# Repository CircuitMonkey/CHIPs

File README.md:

# CHIPs (aka CHIPz)

CHIPz modules are sub-circuits cooked down into a SMT module with a Cyberpunk Tech aesthetic.

The edge contacts are castelated and resemble the edge of a postage stamp.  Like similar modules on the market, CHIPs are designed to be soldered to a larger PCB board.  One advantage of the CHIPz modules is that a design can be revised or re-engineered to improve a larger design without having to redesign the whole system.  CHIPz also makes it convenient to pre-build smaller modules with common or repetive functions and use them over and over in other larger designs.

Almost all of the numbered designs were designed in EagleCAD and were intended to be sold into the hobby electronics market.  Alas, I have given up on that dream, but offer these designs for anyone who wishes to use them or just study the things I have made over the years. My current and future designs are now made with KiCAD.

I still design CHIPz modules and other things, but not for the purpose of manufacturing or selling.  I use the modules in my own creations and wish to share those things for anyone who has a similar need or wishes to simply understand the workings of these things.

If you wish to simply make a module, you can generally upload the Eagle BRD or KiCAD_PCB file directly to [OSH Park PCB](https://OSHPark.com) for preview and fabrication.

Everyting here is open source with minimal (if at all) license requirements.  Copy, mash-up and use to your hearts content.

## NOTE
New designs will be placed in a sub-directory, like [Synth] is.  Older designs will be moved eventually into a sub-folder but for now will dominate the file listing you see.

Enjoy,

Mark Koch  (Circuit Monkey)

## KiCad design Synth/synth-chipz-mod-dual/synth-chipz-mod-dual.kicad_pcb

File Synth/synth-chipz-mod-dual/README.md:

# Synth Module -- VCO/VCF Modulator

This module is a CHIPz implementation of a Modulator core for VCO and VCF functions.  It is originally based on a Modulator circuit from a Moog device.

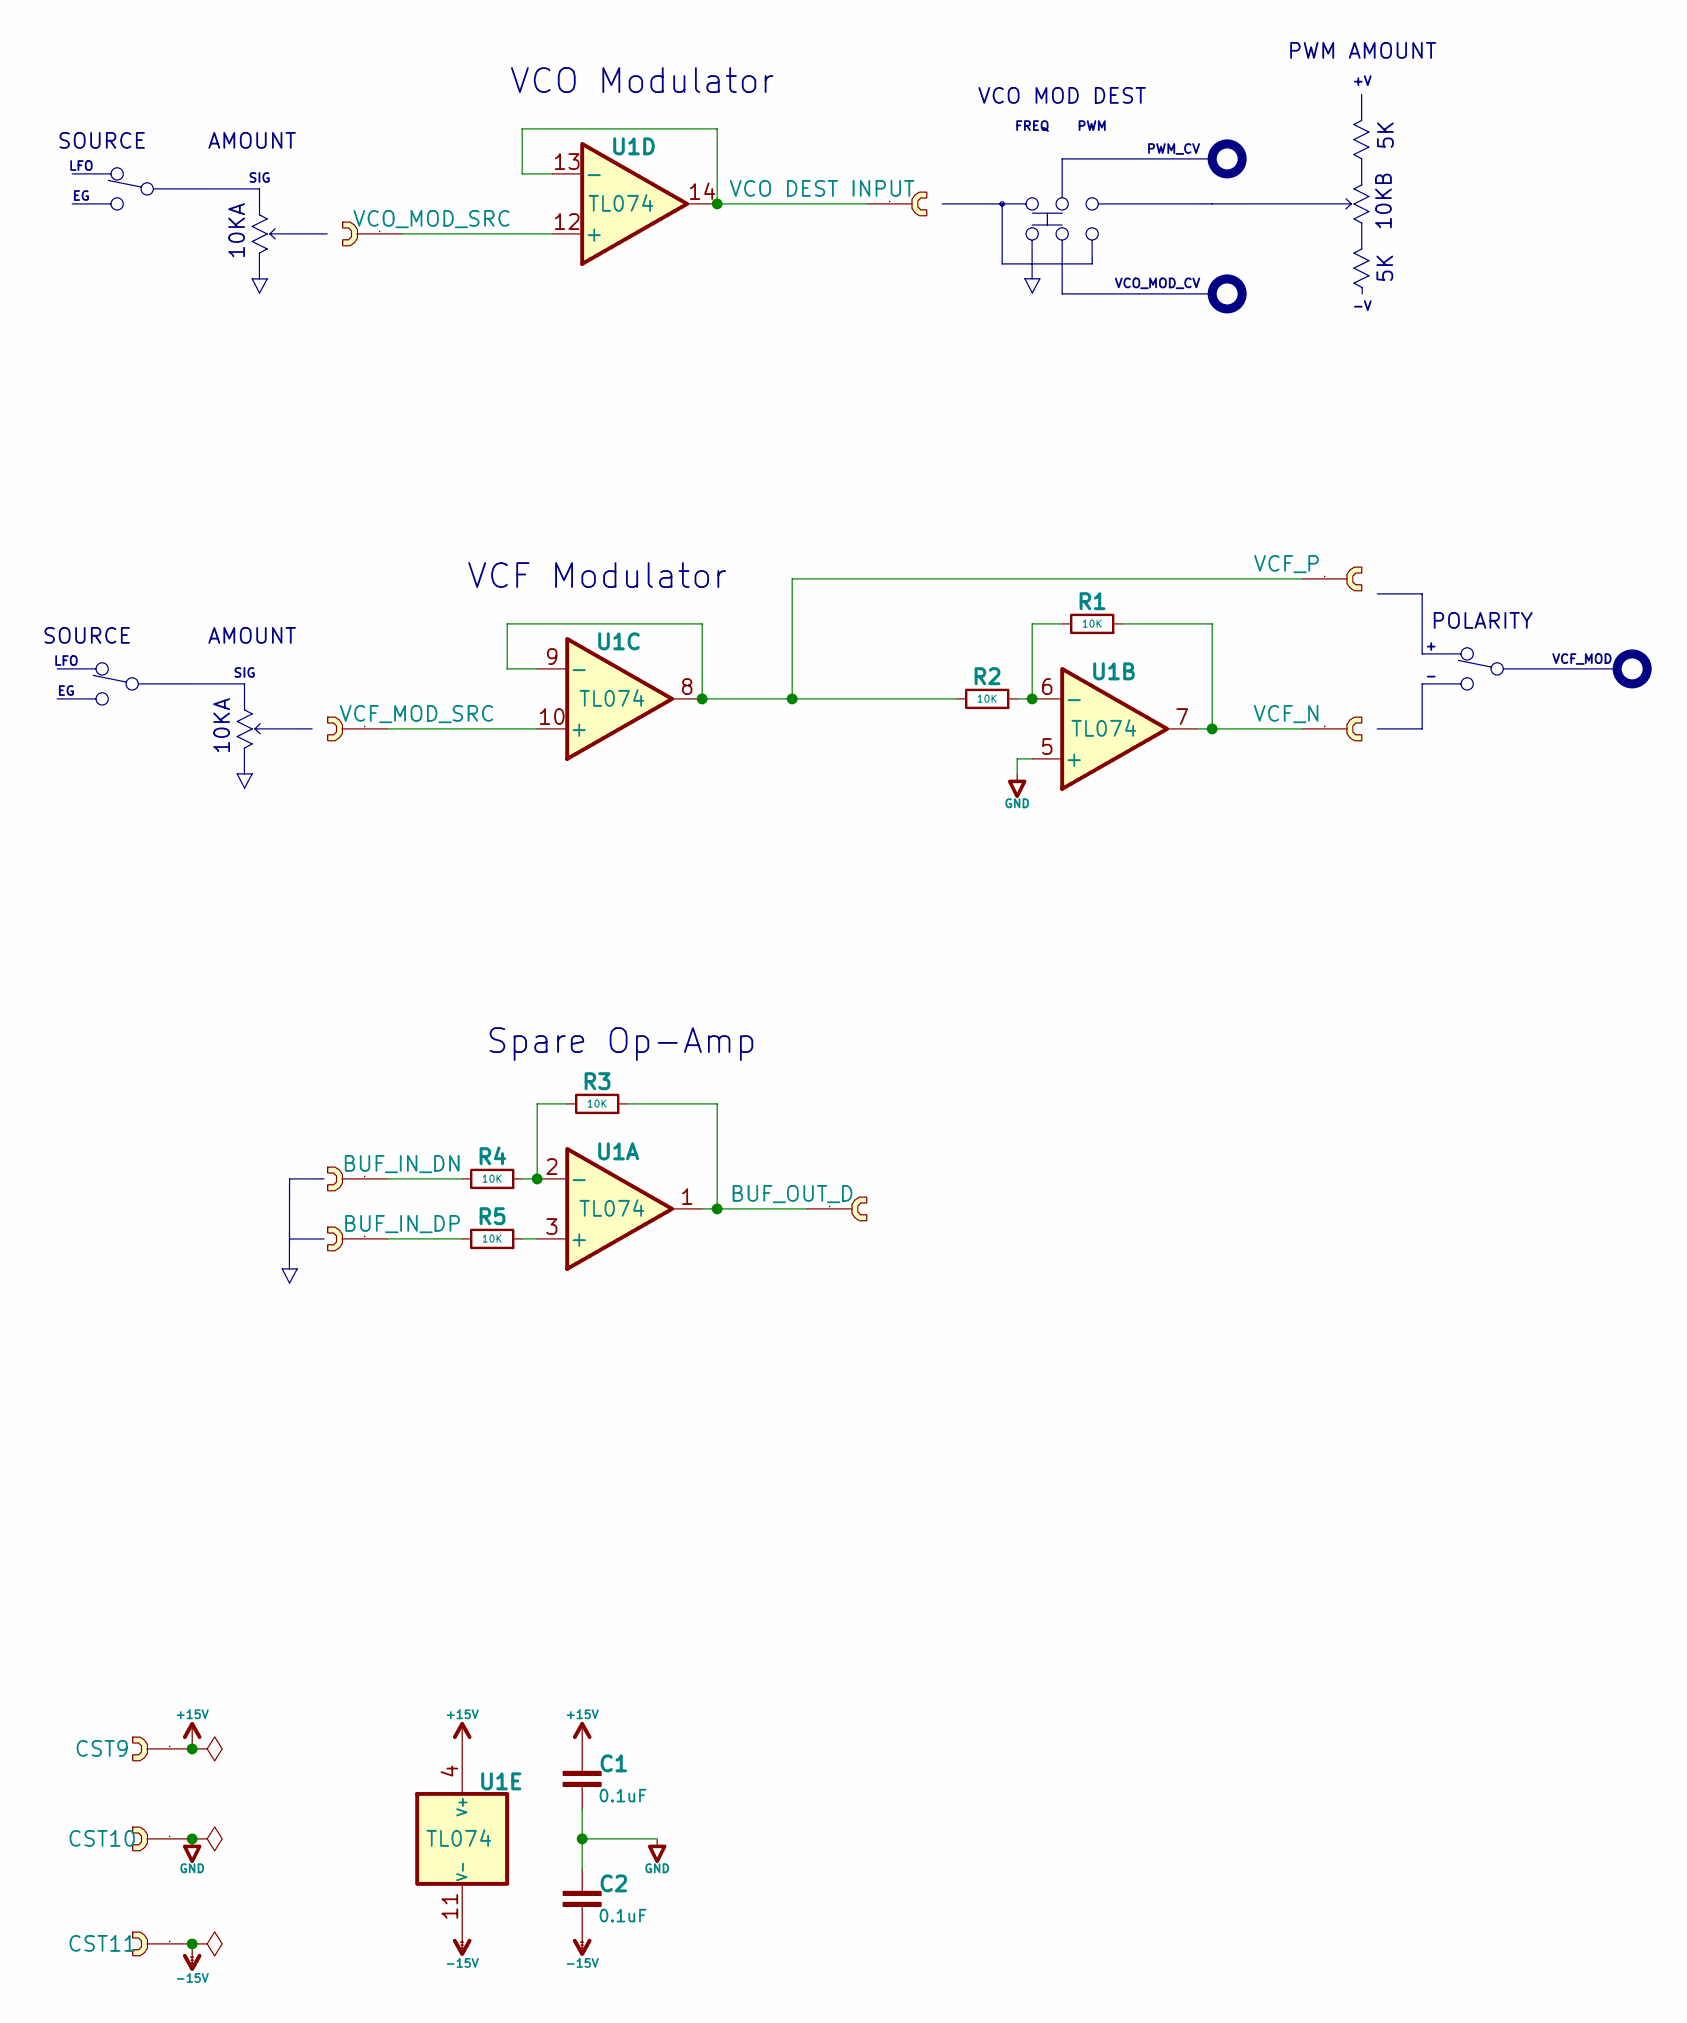
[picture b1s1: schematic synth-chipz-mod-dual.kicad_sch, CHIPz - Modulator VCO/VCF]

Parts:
C1, C2: 0.1uF; C_0603_1608Metric
CST1: VCO DEST INPUT; cast-2.0-01P
CST2: VCO_MOD_SRC; cast-2.0-01P
CST3: VCF_P; cast-2.0-01P
CST4: VCF_MOD_SRC; cast-2.0-01P
CST5: VCF_N; cast-2.0-01P
CST6: BUF_IN_DN; cast-2.0-01P
CST7: BUF_OUT_D; cast-2.0-01P
CST8: BUF_IN_DP; cast-2.0-01P
CST9: +V; cast-2.0-01P
CST10: GND; cast-2.0-01P
CST11: -V; cast-2.0-01P
R1, R2, R3, R4, R5: 10K; R_0603_1608Metric
U1: TL074; SO-14_3.9x8.65mm_P1.27mm; MPN TL074HIDR

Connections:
+15V: C1.1, CST9.1, U1.4 (V+)
-15V: C2.2, CST11.1, U1.11 (V-)
GND: C1.2, C2.1, CST10.1, U1.5 (+)
unnamed: CST5.1, R1.1, U1.7
unnamed: CST6.1, R4.2
unnamed: CST7.1, R3.1, U1.1
unnamed: CST8.1, R5.2
unnamed: R5.1, U1.3 (+)
unnamed: R3.2, R4.1, U1.2 (-)
unnamed: R1.2, R2.1, U1.6 (-)
unnamed: CST4.1, U1.10 (+)
unnamed: CST3.1, R2.2, U1.8, U1.9 (-)
unnamed: CST2.1, U1.12 (+)
unnamed: CST1.1, U1.13 (-), U1.14

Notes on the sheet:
VCO Modulator
10KB
Spare Op-Amp
SIG
SOURCE
FREQ
VCF_MOD
POLARITY
PWM_CV
VCF Modulator
VCO_MOD_CV
VCO MOD DEST
LFO
AMOUNT
PWM AMOUNT
10KA
PWM

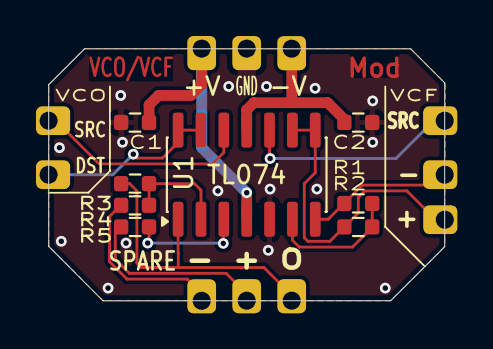
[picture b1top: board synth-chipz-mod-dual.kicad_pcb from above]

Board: 2 copper layers, 22.0 x 14.0 mm, 19 parts (0 on the bottom side), 14 nets.

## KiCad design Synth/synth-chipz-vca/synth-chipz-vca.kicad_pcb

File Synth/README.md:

# CHIPz -- Synth Modules

I'm moving away from part numbers and grouping new designs by purpose.

The boards here are for sound synthesizer designs and many are used in my
ASMR (Advanced Synth Modular Rack) system.

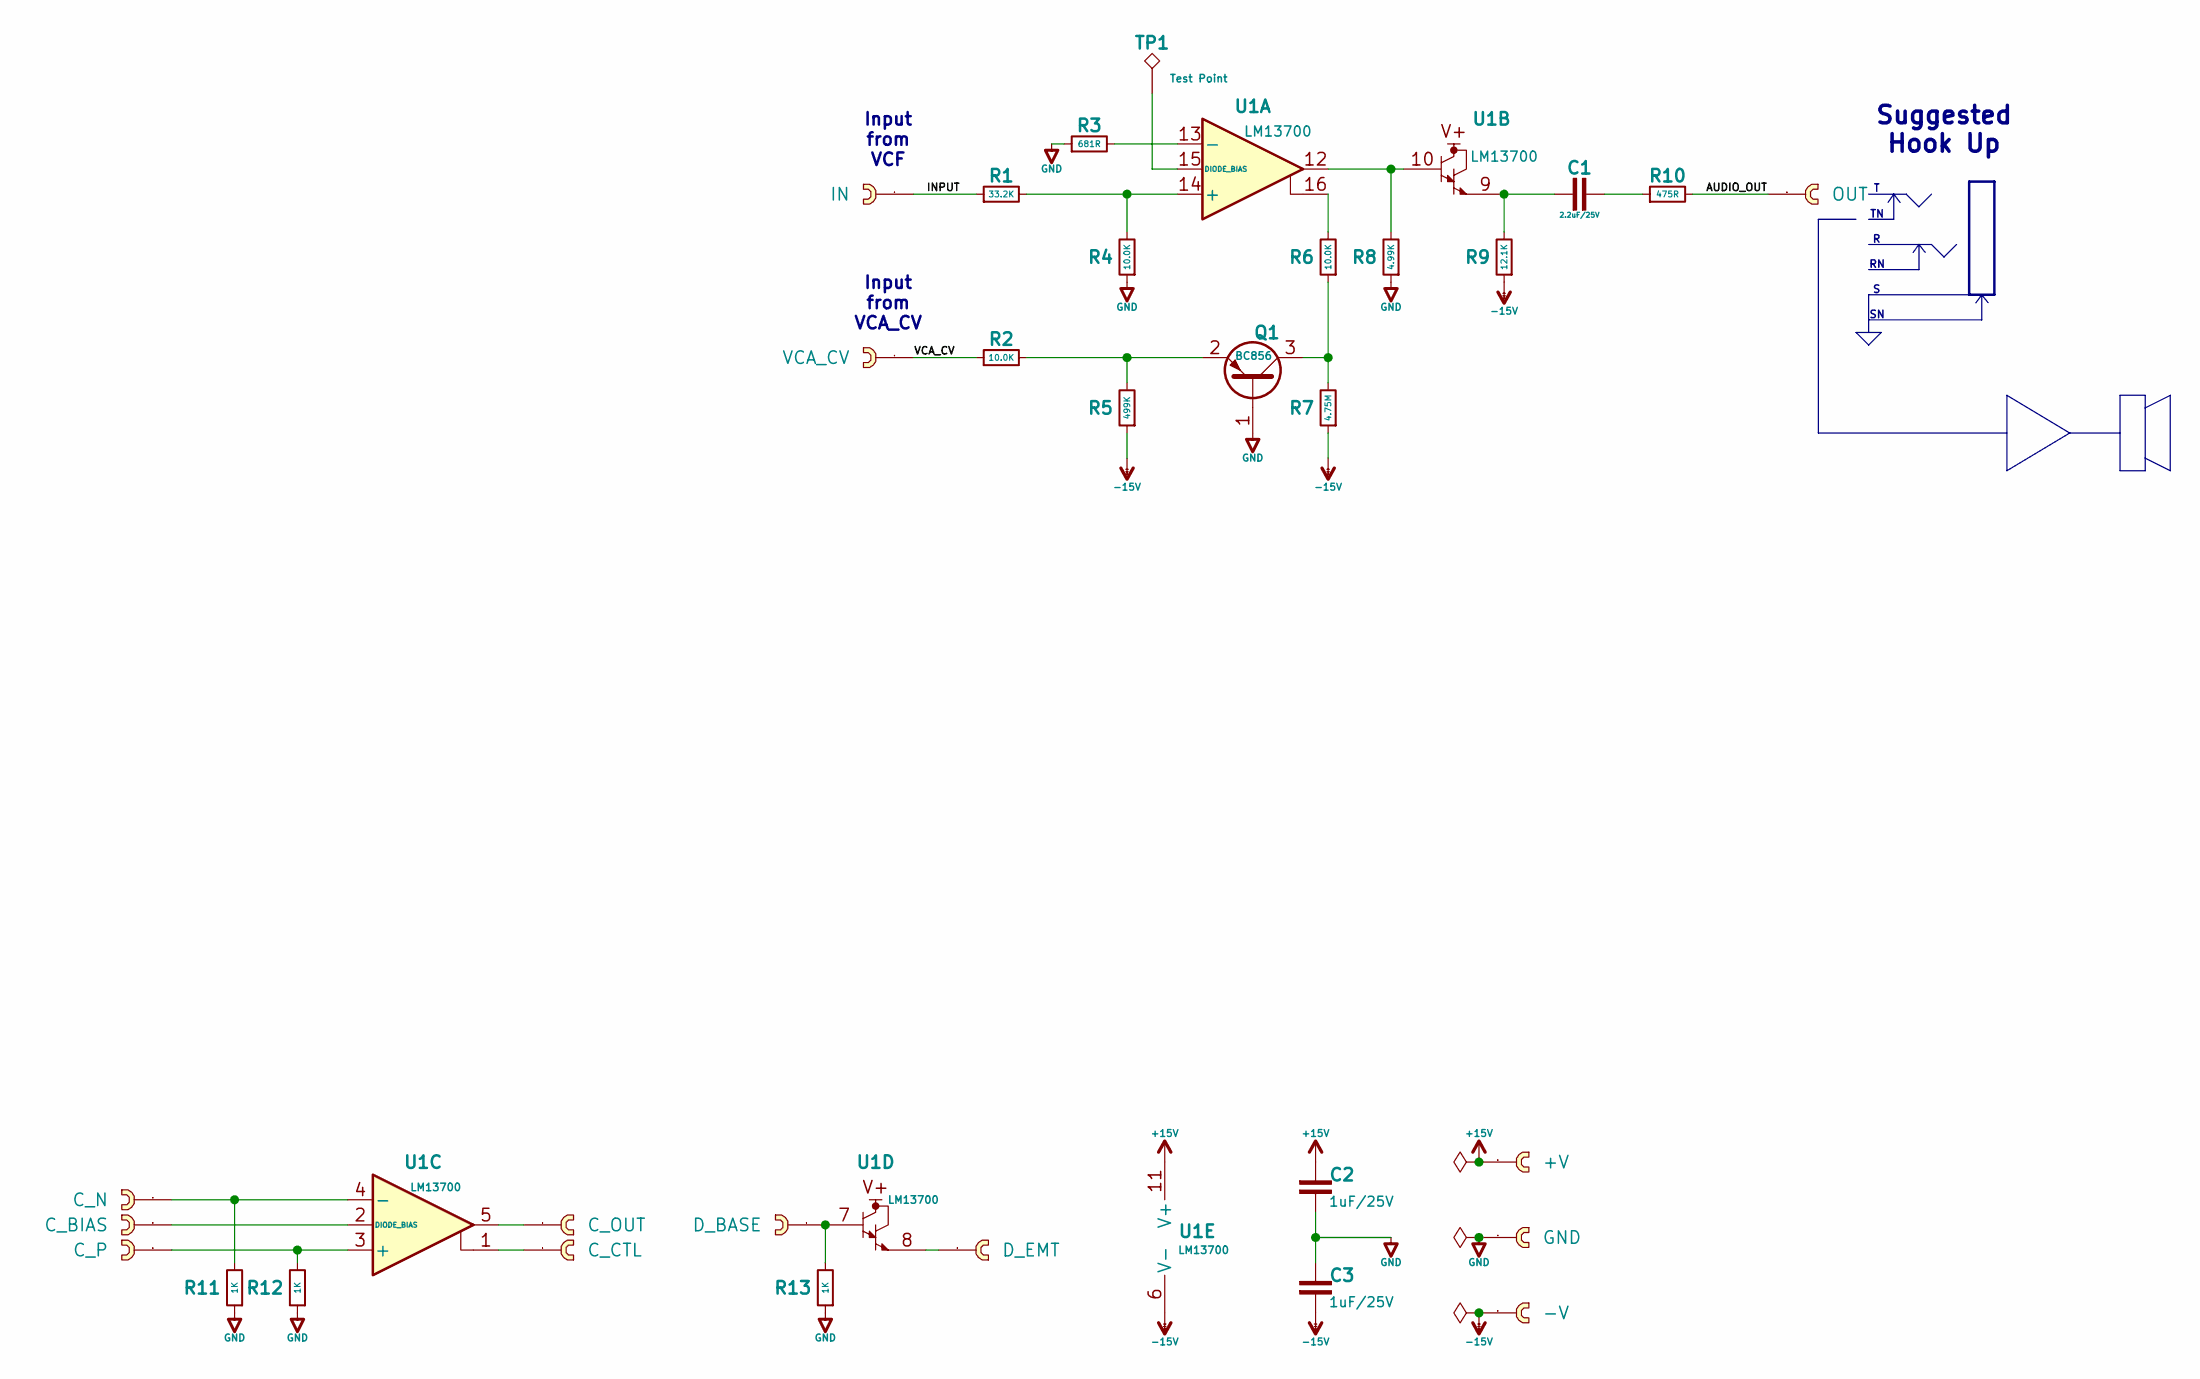
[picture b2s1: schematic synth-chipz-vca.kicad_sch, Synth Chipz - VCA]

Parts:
C1: 2.2uF/25V; C_0603_1608Metric
C2, C3: 1uF/25V; C_0603_1608Metric
CST1: IN; cast-2.0-01P
CST2: VCA_CV; cast-2.0-01P
CST3: OUT; cast-2.0-01P
CST4: C_N; cast-2.0-01P
CST5: C_BIAS; cast-2.0-01P
CST6: C_P; cast-2.0-01P
CST7: C_OUT; cast-2.0-01P
CST8: C_CTL; cast-2.0-01P
CST9: D_BASE; cast-2.0-01P
CST10: D_EMT; cast-2.0-01P
CST11: +V; cast-2.0-01P
CST12: GND; cast-2.0-01P
CST13: -V; cast-2.0-01P
Q1: BC856; SOT-23
R1: 33.2K; R_0603_1608Metric
R2, R4, R6: 10.0K; R_0603_1608Metric
R3: 681R; R_0603_1608Metric
R5: 499K; R_0603_1608Metric
R7: 4.75M; R_0603_1608Metric
R8: 4.99K; R_0603_1608Metric
R9: 12.1K; R_0603_1608Metric
R10: 475R; R_0603_1608Metric
R11, R12, R13: 1K; R_0603_1608Metric
TP1: Test Point; TestPoint_Pad_D1.5mm
U1: LM13700; SO-16_3.9x9.9mm_P1.27mm

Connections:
+15V: C2.1, CST11.1, U1.11 (V+)
-15V: C3.2, CST13.1, R5.1, R7.1, R9.1, U1.6 (V-)
/AUDIO_OUT: CST3.1, R10.2
/INPUT: CST1.1, R1.1
/VCA_CV: CST2.1, R2.1
GND: C2.2, C3.1, CST12.1, Q1.1 (B), R3.1, R4.1, R8.1, R11.1, R12.1, R13.1
unnamed: C1.1, R9.2, U1.9
unnamed: C1.2, R10.1
unnamed: CST7.1, U1.5
unnamed: CST8.1, U1.1
unnamed: CST9.1, R13.2, U1.7
unnamed: CST10.1, U1.8
unnamed: Q1.3 (C), R6.1, R7.2
unnamed: Q1.2 (E), R2.2, R5.2
unnamed: R6.2, U1.16
unnamed: R8.2, U1.10, U1.12
unnamed: R1.2, R4.2, U1.14 (+)
unnamed: R3.2, U1.13 (-)
unnamed: TP1.1, U1.15 (DIODE_BIAS)
unnamed: CST6.1, R12.2, U1.3 (+)
unnamed: CST4.1, R11.2, U1.4 (-)
unnamed: CST5.1, U1.2 (DIODE_BIAS)

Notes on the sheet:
Input from VCF
Input from VCA_CV
Suggested Hook Up

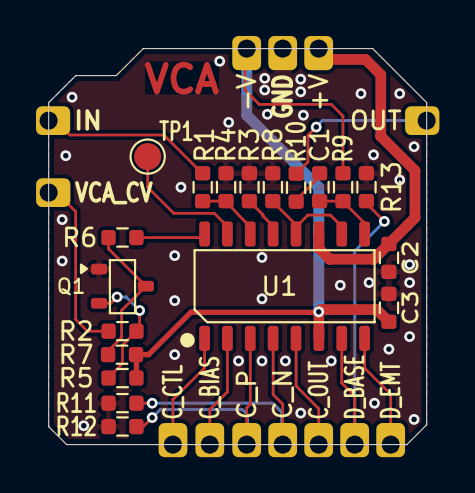
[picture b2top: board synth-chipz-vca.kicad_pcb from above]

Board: 2 copper layers, 21.0 x 22.0 mm, 32 parts (0 on the bottom side), 22 nets.

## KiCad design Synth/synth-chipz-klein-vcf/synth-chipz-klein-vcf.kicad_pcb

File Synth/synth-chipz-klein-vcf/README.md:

# Synth Module -- Diode Ladder VCF

This module is a CHIPz implementation of a Diode Ladder Voltage Controlled Filter designed by
Moritz Klein and it's theory of operation is described in detail in a [YouTube video](https://www.youtube.com/watch?v=jvNNgUl3al0).

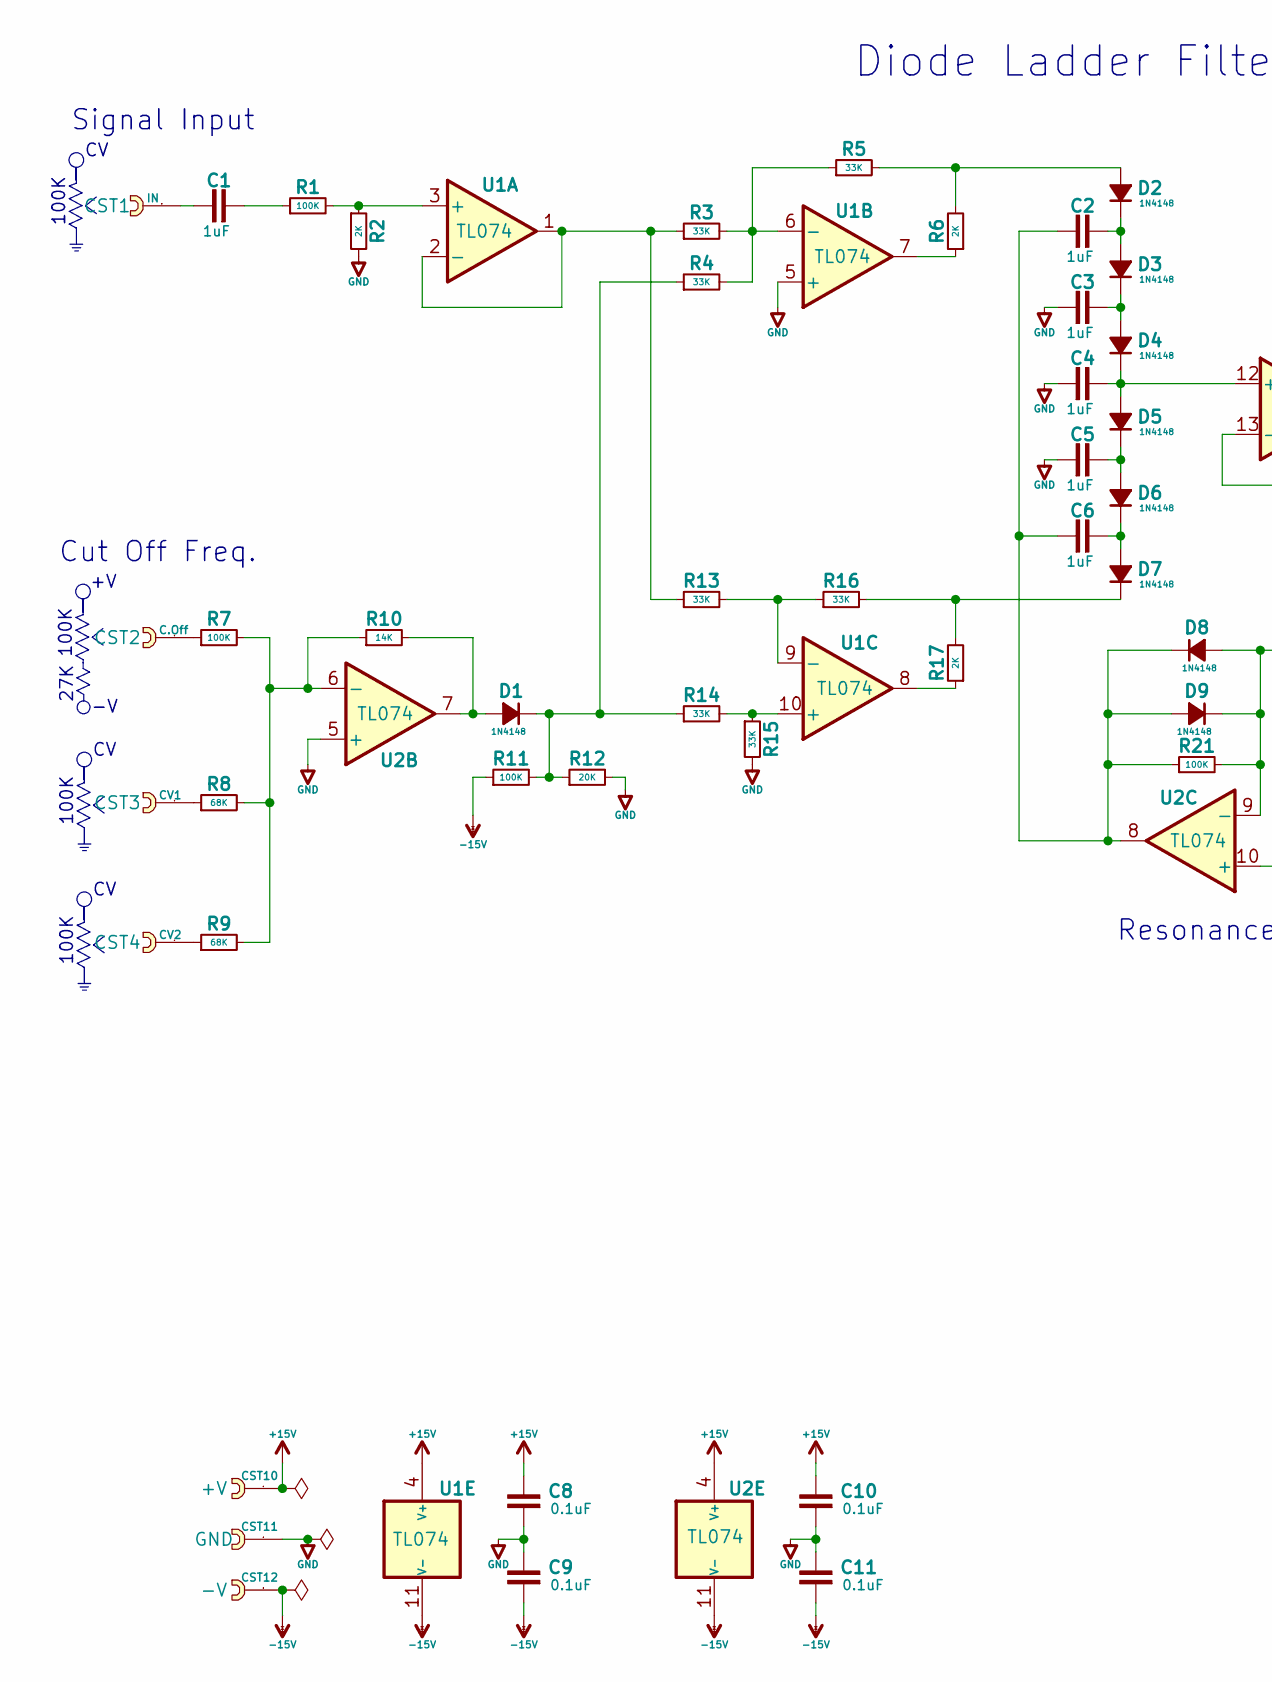
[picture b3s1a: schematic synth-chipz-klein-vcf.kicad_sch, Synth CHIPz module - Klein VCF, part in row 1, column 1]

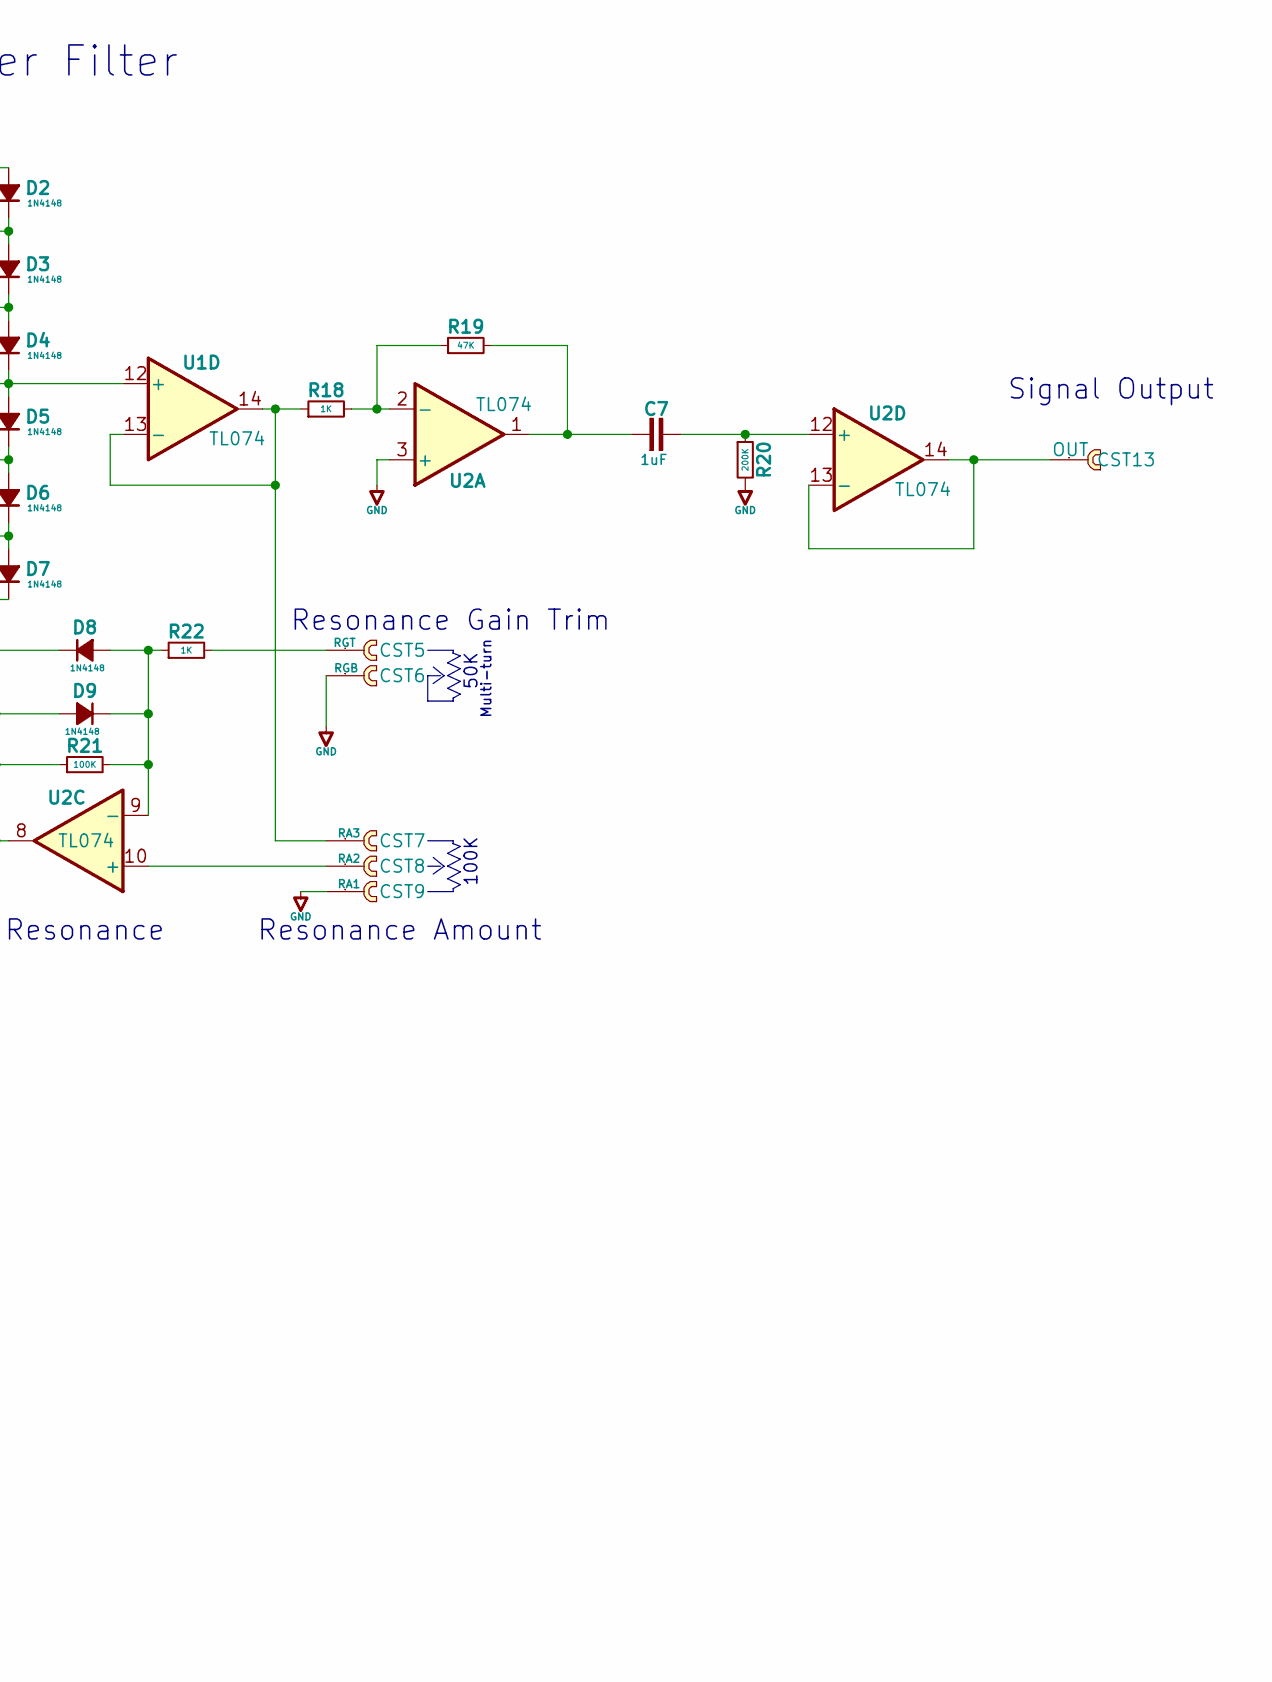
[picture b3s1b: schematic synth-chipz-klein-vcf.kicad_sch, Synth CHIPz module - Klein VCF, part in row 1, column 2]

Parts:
C1, C2, C3, C4, C5, C6, C7: 1uF; C_0603_1608Metric
C8, C9, C10, C11: 0.1uF; C_0603_1608Metric
CST1: IN; cast-2.0-01P
CST2: C.Off; cast-2.0-01P
CST3: CV1; cast-2.0-01P
CST4: CV2; cast-2.0-01P
CST5: RGT; cast-2.0-01P
CST6: RGB; cast-2.0-01P
CST7: RA3; cast-2.0-01P
CST8: RA2; cast-2.0-01P
CST9: RA1; cast-2.0-01P
CST10: +V; cast-2.0-01P
CST11: GND; cast-2.0-01P
CST12: -V; cast-2.0-01P
CST13: OUT; cast-2.0-01P
D1, D2, D3, D4, D5, D6, D7, D8, D9: 1N4148; D_SOD-123
R1, R7, R11, R21: 100K; R_0603_1608Metric
R2, R6, R17: 2K; R_0603_1608Metric
R3, R4, R5, R13, R14, R15, R16: 33K; R_0603_1608Metric
R8, R9: 68K; R_0603_1608Metric
R10: 14K; R_0603_1608Metric
R12: 20K; R_0603_1608Metric
R18, R22: 1K; R_0603_1608Metric
R19: 47K; R_0603_1608Metric
R20: 200K; R_0603_1608Metric
U1, U2: TL074; SO-14_3.9x8.65mm_P1.27mm; MPN TL074HIDR

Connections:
+15V: C8.2, C10.2, CST10.1, U1.4 (V+), U2.4 (V+)
-15V: C9.1, C11.1, CST12.1, R11.1, U1.11 (V-), U2.11 (V-)
GND: C3.1, C4.1, C5.1, C8.1, C9.2, C10.1, C11.2, CST6.1, CST9.1, CST11.1, R2.2, R12.2, R15.2, R20.2, U1.5 (+), U2.3 (+), U2.5 (+)
unnamed: C1.1, CST1.1
unnamed: C1.2, R1.1
unnamed: C7.1, R19.2, U2.1
unnamed: CST2.1, R7.1
unnamed: CST3.1, R8.1
unnamed: CST4.1, R9.1
unnamed: CST5.1, R22.2
unnamed: D1.2 (A), R10.2, U2.7
unnamed: D1.1 (K), R4.1, R11.2, R12.1, R14.1
unnamed: D2.2 (A), R5.2, R6.2
unnamed: C2.2, D2.1 (K), D3.2 (A)
unnamed: C3.2, D3.1 (K), D4.2 (A)
unnamed: C4.2, D4.1 (K), D5.2 (A), U1.12 (+)
unnamed: C5.2, D5.1 (K), D6.2 (A)
unnamed: C6.2, D6.1 (K), D7.2 (A)
unnamed: D7.1 (K), R16.2, R17.2
unnamed: D8.2 (A), D9.1 (K), R21.2, R22.1, U2.9 (-)
unnamed: C2.1, C6.1, D8.1 (K), D9.2 (A), R21.1, U2.8
unnamed: R6.1, U1.7
unnamed: R17.1, U1.8
unnamed: R1.2, R2.1, U1.3 (+)
unnamed: R3.1, R13.1, U1.1, U1.2 (-)
unnamed: R3.2, R4.2, R5.1, U1.6 (-)
unnamed: R14.2, R15.1, U1.10 (+)
unnamed: R13.2, R16.1, U1.9 (-)
unnamed: CST7.1, R18.1, U1.13 (-), U1.14
unnamed: R18.2, R19.1, U2.2 (-)
unnamed: R7.2, R8.2, R9.2, R10.1, U2.6 (-)
unnamed: CST8.1, U2.10 (+)
unnamed: C7.2, R20.1, U2.12 (+)
unnamed: CST13.1, U2.13 (-), U2.14

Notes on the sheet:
100K
Resonance
Cut Off Freq.
Resonance Gain Trim
Signal Input
Diode Ladder Filter
Multi-turn
27K
Resonance Amount
50K
Signal Output

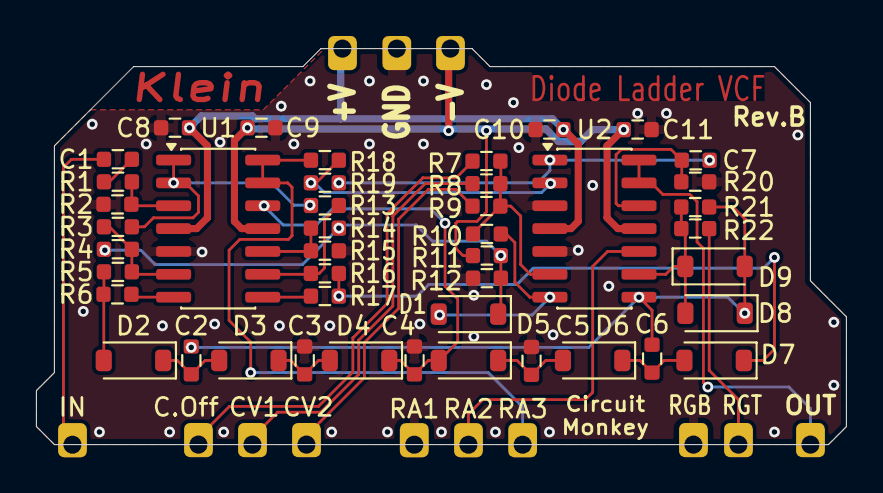
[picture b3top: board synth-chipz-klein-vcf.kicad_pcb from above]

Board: 2 copper layers, 45.0 x 22.0 mm, 57 parts (0 on the bottom side), 34 nets.

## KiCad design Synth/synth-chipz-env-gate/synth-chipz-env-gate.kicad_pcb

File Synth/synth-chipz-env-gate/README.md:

# Synth Module -- Envelope Gate

This module is a CHIPz implementation of a Envelope Gate. Featuring Attack and Decay controls.

The design is based on a Moog circuit.

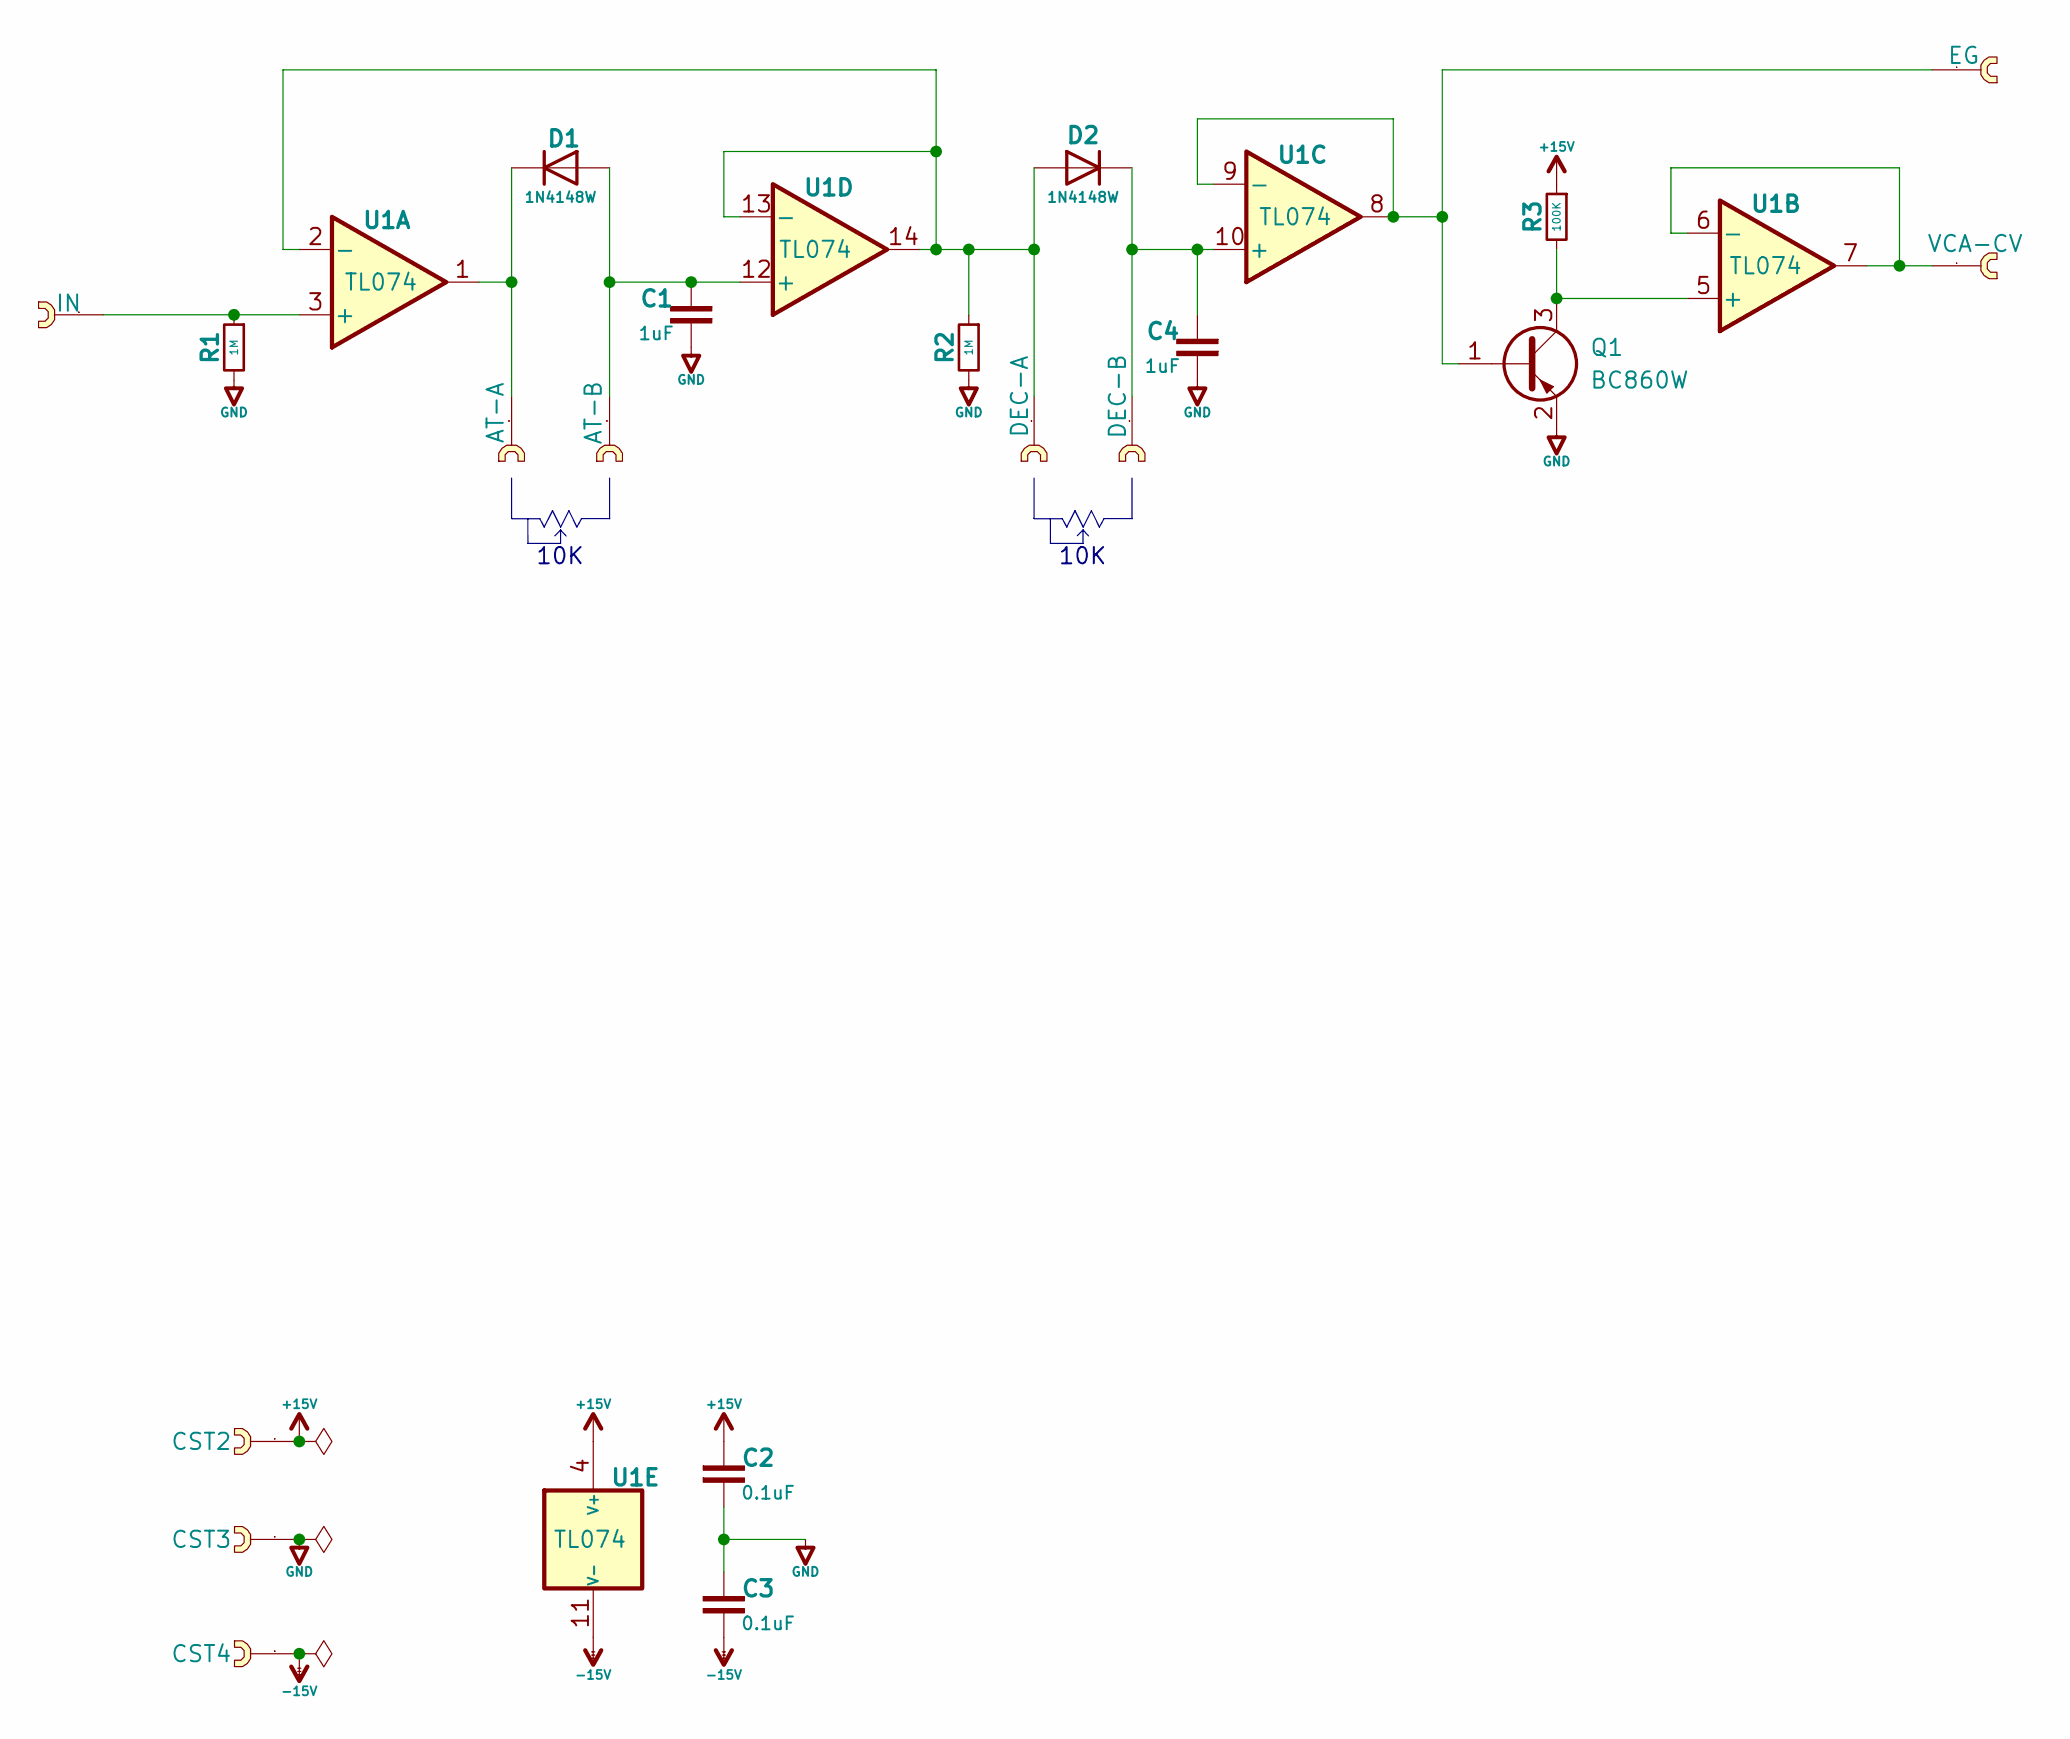
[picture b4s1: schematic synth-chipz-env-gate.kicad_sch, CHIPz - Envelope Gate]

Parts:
C1, C4: 1uF; C_0603_1608Metric
C2, C3: 0.1uF; C_0603_1608Metric
CST1: IN; cast-2.0-01P
CST2: +V; cast-2.0-01P
CST3: GND; cast-2.0-01P
CST4: -V; cast-2.0-01P
CST5: AT-A; cast-2.0-01P
CST6: AT-B; cast-2.0-01P
CST7: DEC-A; cast-2.0-01P
CST8: DEC-B; cast-2.0-01P
CST9: EG; cast-2.0-01P
CST10: VCA-CV; cast-2.0-01P
D1, D2: 1N4148W; D_SOD-123
Q1: BC860W; SOT-323_SC-70
R1, R2: 1M; R_0603_1608Metric
R3: 100K; R_0603_1608Metric
U1: TL074; SO-14_3.9x8.65mm_P1.27mm; MPN TL074HIDR

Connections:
+15V: C2.1, CST2.1, R3.1, U1.4 (V+)
-15V: C3.2, CST4.1, U1.11 (V-)
GND: C1.2, C2.2, C3.1, C4.2, CST3.1, Q1.2 (E), R1.2, R2.2
unnamed: C1.1, CST6.1, D1.2 (A), U1.12 (+)
unnamed: CST5.1, D1.1 (K), U1.1
unnamed: CST7.1, D2.2 (A), R2.1, U1.2 (-), U1.13 (-), U1.14
unnamed: C4.1, CST8.1, D2.1 (K), U1.10 (+)
unnamed: CST9.1, Q1.1 (B), U1.8, U1.9 (-)
unnamed: Q1.3 (C), R3.2, U1.5 (+)
unnamed: CST1.1, R1.1, U1.3 (+)
unnamed: CST10.1, U1.6 (-), U1.7

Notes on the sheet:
10K

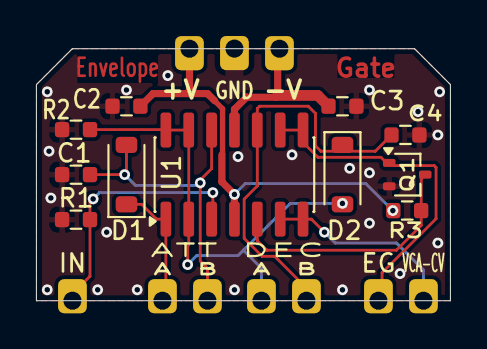
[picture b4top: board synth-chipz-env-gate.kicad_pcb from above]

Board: 2 copper layers, 23.0 x 14.0 mm, 21 parts (0 on the bottom side), 11 nets.

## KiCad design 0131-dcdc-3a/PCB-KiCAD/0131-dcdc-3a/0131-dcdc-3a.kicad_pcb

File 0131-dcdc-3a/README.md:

# Circuit Monkey CHIPs &#35;0131 -- DCDC Converter 1.8V-5V@2A-3A

## Description
DC Buck Voltage converter.  Default config is 5V at 3Amps but capable of 1.8V to 5V range (using specific feedback resistor values) and current range of 2A - 3A max using alternative chip part numbers.

Features TSOP26 size package.   Our 0121A model is this same circuit but uses the SOT563 (smaller) package.  Note: Pinout is reversed for 0121 model.

## Images

## Technical Details
* **Dimensions:** 11.5mm wide x 9mm tall  x 0.8mm PCB thickness
* **Pad Style:** Castellated Pin Edges allow easy surface mounting as well as hand wiring
* **Pad Pitch:** Minimum Pad Pitch is 2.0mm
* **Chip, 3A:** Diodes Inc. [AP62300 DCDC Converter](https://www.diodes.com/assets/Datasheets/AP62300_AP62301_AP62300T.pdf)
* **Chip, 2A:** Diodes Inc. [AP62200 DCDC Converter](https://www.diodes.com/assets/Datasheets/AP62200_AP62201_AP62200T.pdf)

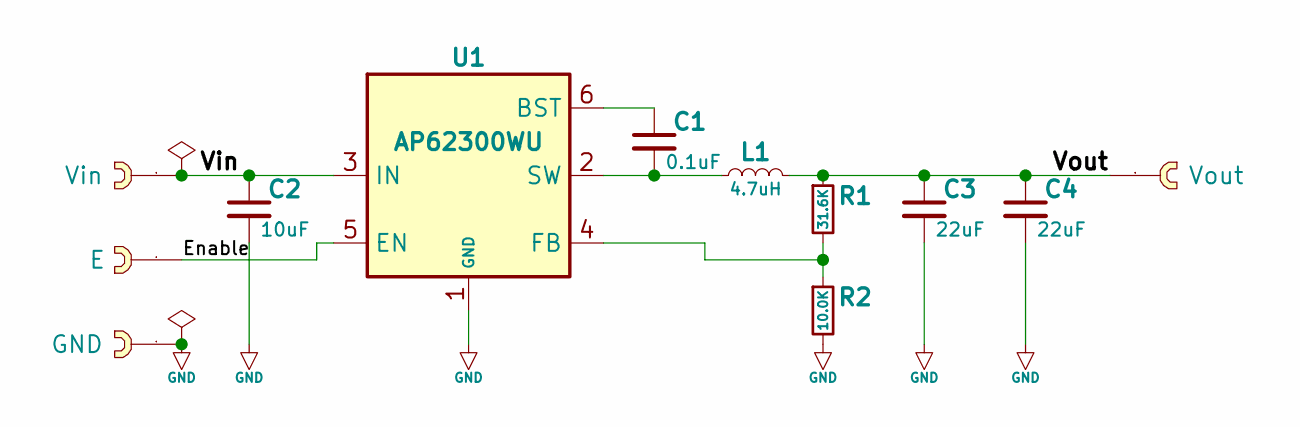
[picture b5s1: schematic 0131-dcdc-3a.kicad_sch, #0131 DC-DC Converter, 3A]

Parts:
C1: 0.1uF; C_0603_1608Metric
C2: 10uF; C_0603_1608Metric
C3, C4: 22uF; C_0603_1608Metric
CST1: Vin; cast-2.0-01P
CST2: Vout; cast-2.0-01P
CST3: E; cast-2.0-01P
CST4: GND; cast-2.0-01P
L1: 4.7uH; SRN5040
R1: 31.6K; R_0603_1608Metric
R2: 10.0K; R_0603_1608Metric
U1: AP62300WU; TSOT-23-6

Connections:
/Enable: CST3.1, U1.5 (EN)
/Vin: C2.1, CST1.1, U1.3 (IN)
/Vout: C3.1, C4.1, CST2.1, L1.2, R1.1
GND: C2.2, C3.2, C4.2, CST4.1, R2.2, U1.1 (GND)
unnamed: C1.1, U1.6 (BST)
unnamed: R1.2, R2.1, U1.4 (FB)
unnamed: C1.2, L1.1, U1.2 (SW)

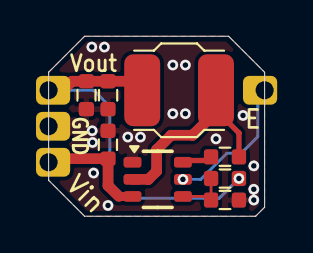
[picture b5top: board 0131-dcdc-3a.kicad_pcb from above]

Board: 2 copper layers, 12.0 x 10.0 mm, 12 parts (0 on the bottom side), 7 nets.

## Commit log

2021-02-23 Push the Rev. A boards to GIT hub.
2021-02-23 Update BOM, Schematic, README, 3rd Party PDFs
2021-02-23 Move PCB designs into their proper sub-directories.
2021-02-24 Update Documents
2021-02-24 Rename 0117 Preview images to include revision
2021-02-24 Correct link to preview images
2021-02-28 Rename 0116 to 0116-class-d-amp. Add 3D renders for each CHIP.
2021-02-28 Update how images look on Readme page
2021-03-12 New boards. Created 0119 BOM.
2021-03-12 Update Readme for 0124 and 0125.
2021-03-12 Fix typo in image link.
2021-03-12 3rd Party directory was improperly named.
2021-03-12 Add preview Images for 0124A and 0125A
2021-03-12 Rename preview image to include revision
2021-03-22 Create DESCRIPTION
2021-07-29 CHIPs work in progress
2022-07-02 Made four channel FET for lower power applications.
2022-07-02 Create carrier for 0119 m328p module
2022-07-04 Big batch of new PCBs sent to FAB.
2022-07-06 Retire part number for 0123 test board.
    Probably will never make this board.
2022-07-06 Create 0123 Class-D amp CHIP and carrier board.
2022-07-06 Create 0127 SD-Card CHIP and carrier board.
2022-07-11 Pos/Neg Booster board and carrier
2022-07-11 Added 3D models.
2022-07-18 0129 Codec for MP3/MIDI
2022-07-23 Add 0131 DC Voltage Buck converter
2022-07-23 Update BOM details
2022-07-25 BOM updates
2022-07-25 Create 0131 and carrier
2022-07-25 Create 0132 and carrier
2022-07-29 Updates to library part 0603 resistor
2022-07-29 Updated part from library
2022-07-29 Update C5 value
2022-07-29 Rename new BOM file
2022-07-29 rename BOM file
2022-08-06 BOMs for 0129 and 0229
2022-09-01 Add 8-channel level shifter
2022-09-01 Various updates.
2023-06-19 0234 level shifter carrier PCB
2024-01-31 Created 0135 DCDC pos->neg PCB
2024-02-01 Update Feedback Resistor value.
2024-02-07 Update top-level DESCRIPTION
2025-07-31 Update .gitignore
    Ignore some KiCAD file types.
2025-07-31 Rev B of the #131 DC-DC PCB
2025-07-31 Add #0131-B printed schematic and BOM
2025-07-31 Tune documentation, info block.
2025-07-31 Clean up ignore and CAD pr files.
2025-08-05 Add 3D model to 0131 module.
2025-08-20 Fix part values in schematic.
2025-09-03 Update final parts values.
2025-11-04 Create Synth folder and add Klein VCF design.
2025-11-05 Add README. Some changes related to BOM creation.
2025-11-05 Some changes related to BOM creation settings.
2025-11-05 Create schematic PDF document.
2025-11-05 Changes related to BOM creation settings.
2025-11-05 Add BOMs for Synth CHIPz
2025-11-25 Change recommended pot part values from 10K to 1M.
2025-11-25 Add note regarding faceplate mounts. Bumped Rev. to B.
2025-11-25 Adjust resistor value.
2025-11-25 Correct swapped reference silk for R21,R22. Bump Rev.
2025-11-25 Bump rev to match PCB silk change.
2025-11-25 Add note to highlight swapped resistor value references.
2025-11-26 Create Rev.A of VCA PCB
2025-11-27 Add phantom hookup notes.
2025-11-28 VCF P and N silk were swapped! Fixed.
2025-11-28 Bump Rev to reflect PCB change.
2026-01-14 Add VCA schematic and BOM
2026-01-14 Update KiCAD project settings.

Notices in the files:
Synth/synth-chipz-klein-vcf/synth-chipz-klein-vcf.kicad_pcb:
MIT License
